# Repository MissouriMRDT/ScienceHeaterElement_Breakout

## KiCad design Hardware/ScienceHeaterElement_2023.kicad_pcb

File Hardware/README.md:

# ScienceHeater_2024
Files for Science Heater

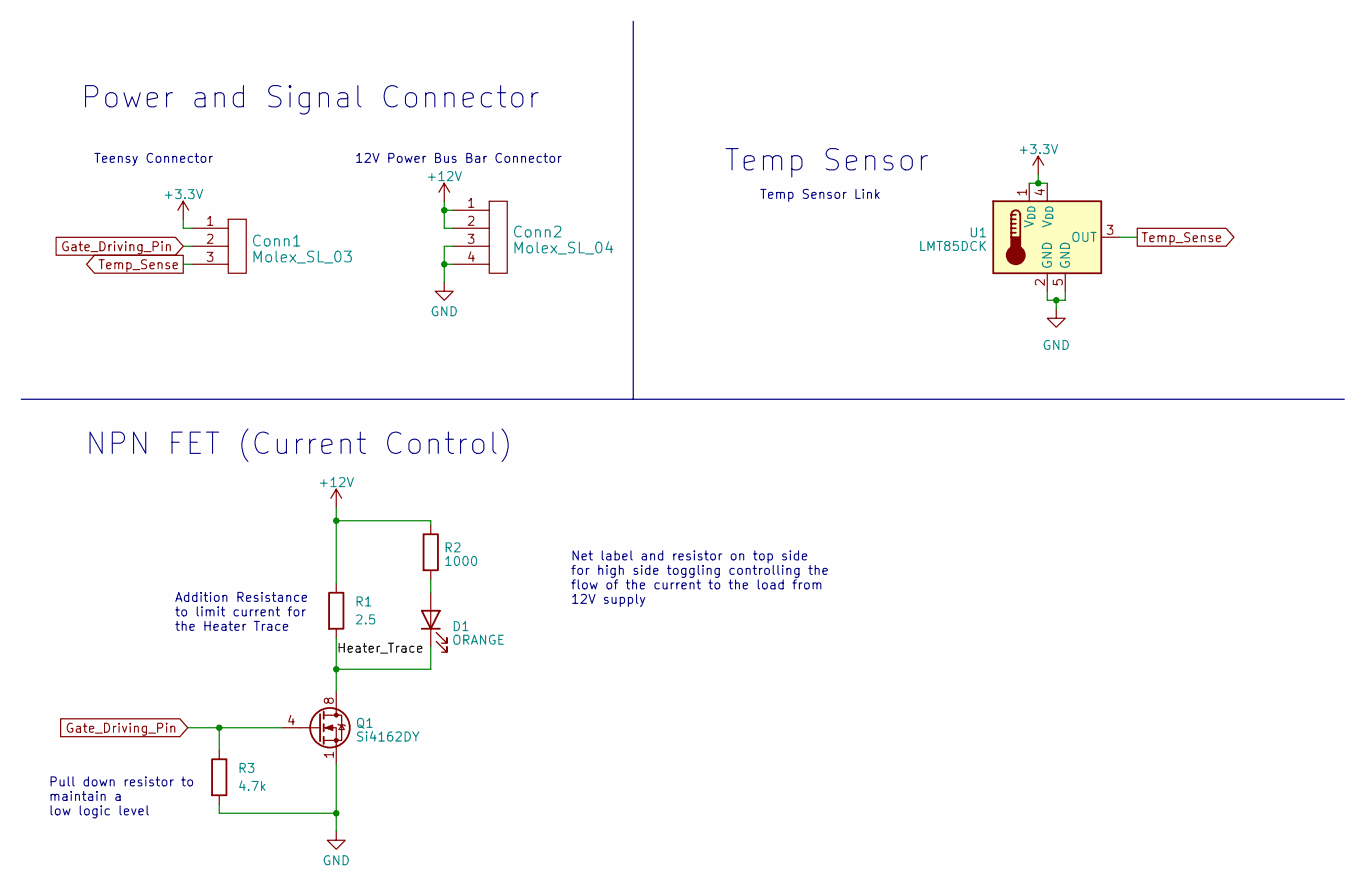
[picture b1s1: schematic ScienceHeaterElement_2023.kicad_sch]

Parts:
Conn1: Molex_SL_03; MOLEX_SL_03_Horizontal
Conn2: Molex_SL_04; MOLEX_SL_04_Horizontal
D1: ORANGE; LED_0603_1608Metric_Pad1.05x0.95mm_HandSolder
Q1: Si4162DY; SOIC-8_3.9x4.9mm_P1.27mm
R1: 2.5; TO-220-2_Horizontal_TabDown
R2: 1000; R_0603_1608Metric_Pad0.98x0.95mm_HandSolder
R3: 4.7k; R_0603_1608Metric_Pad0.98x0.95mm_HandSolder
U1: LMT85DCK; SOT-353_SC-70-5

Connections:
+3.3V: Conn1.1, U1.1 (V_{DD}), U1.4 (V_{DD})
+12V: Conn2.1, Conn2.2, R1.1, R2.1
/Heater_Trace: D1.1 (K), Q1.5 (D), Q1.6 (D), Q1.7 (D), Q1.8 (D), R1.2
GND: Conn2.3, Conn2.4, Q1.1 (S), Q1.2 (S), Q1.3 (S), R3.2, U1.2 (GND), U1.5 (GND)
Gate_Driving_Pin: Conn1.2, Q1.4 (G), R3.1
unnamed: D1.2 (A), R2.2
Temp_Sense: Conn1.3, U1.3 (OUT)

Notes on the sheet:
Addition Resistance to limit current for the Heater Trace
12V Power Bus Bar Connector
Net label and resistor on top side for high side toggling controlling the flow of the current to the load from 12V supply
Temp Sensor Link
Teensy Connector
Power and Signal Connector
NPN FET (Current Control)
Temp Sensor
Pull down resistor to maintain a low logic level

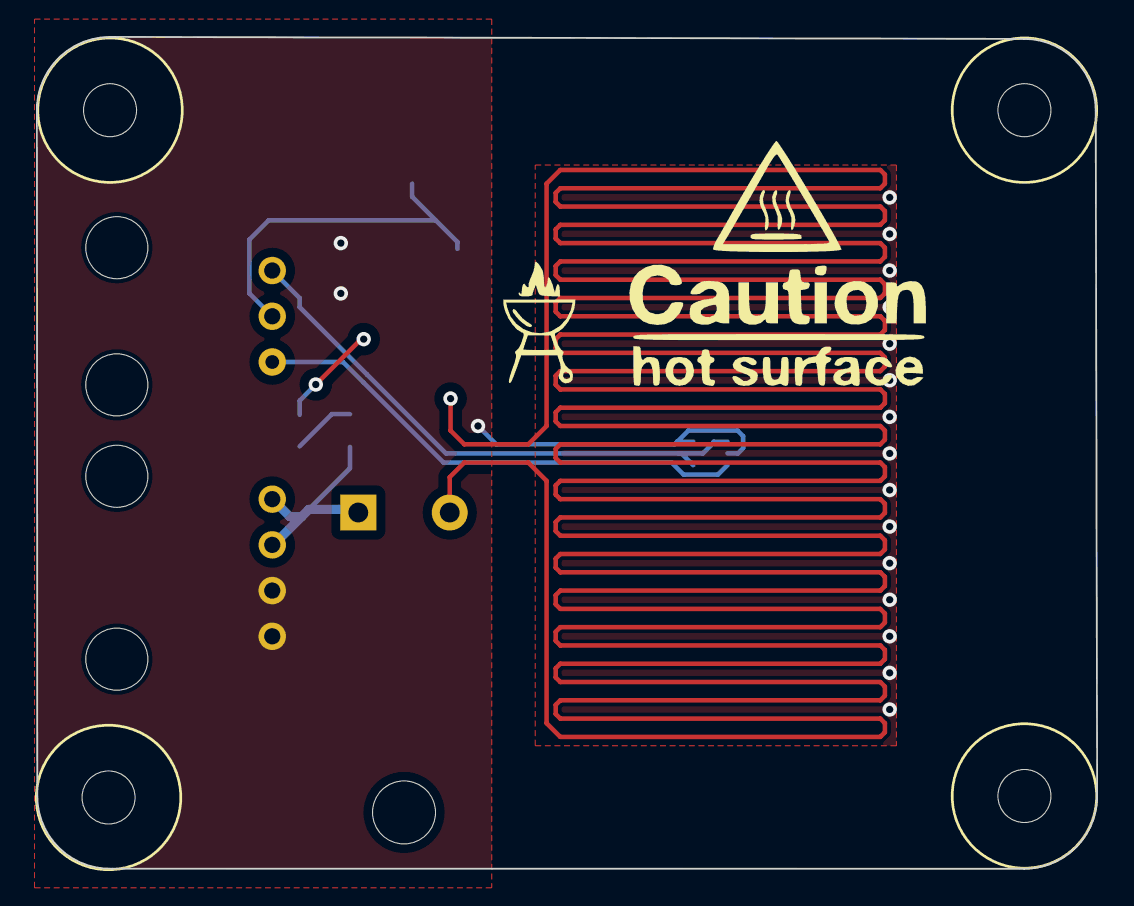
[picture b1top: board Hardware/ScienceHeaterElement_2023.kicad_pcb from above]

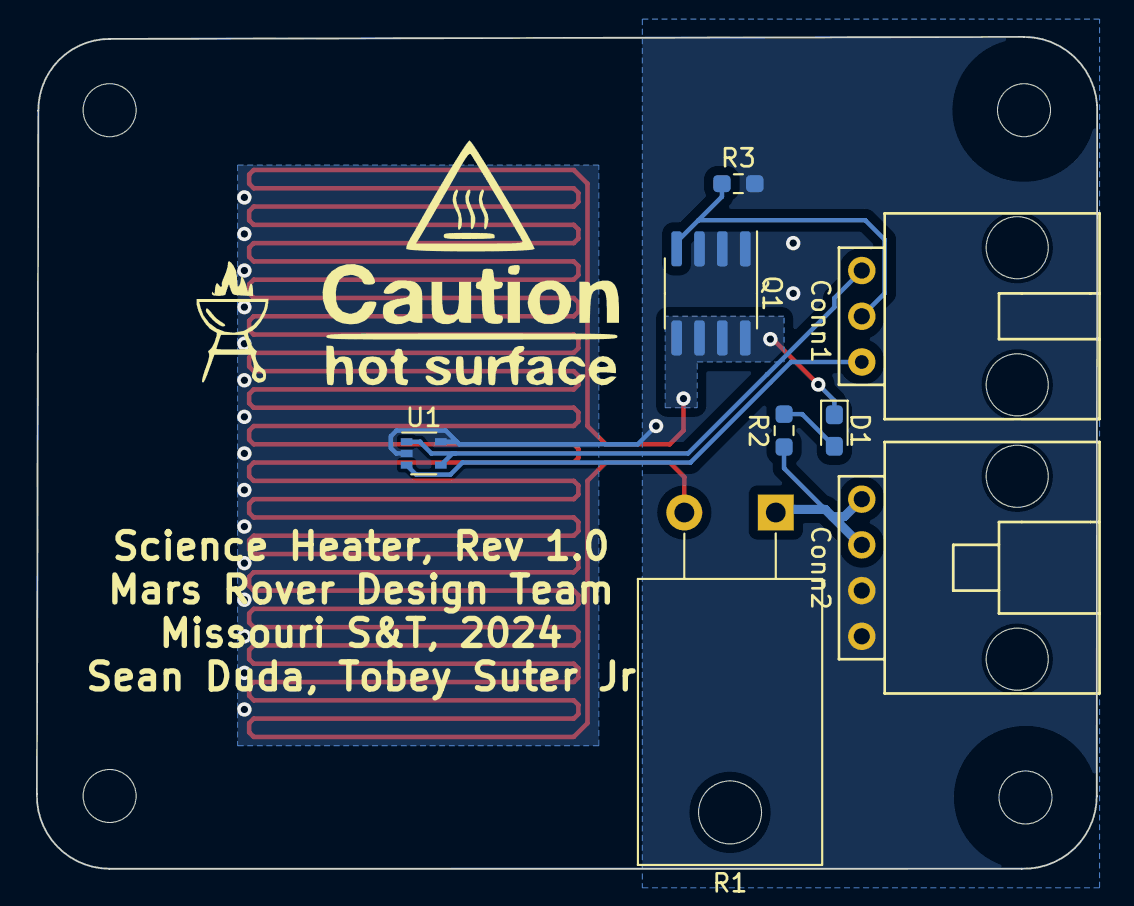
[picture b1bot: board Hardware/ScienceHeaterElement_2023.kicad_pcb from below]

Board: 2 copper layers, 58.9 x 46.2 mm, 8 parts (8 on the bottom side), 7 nets.

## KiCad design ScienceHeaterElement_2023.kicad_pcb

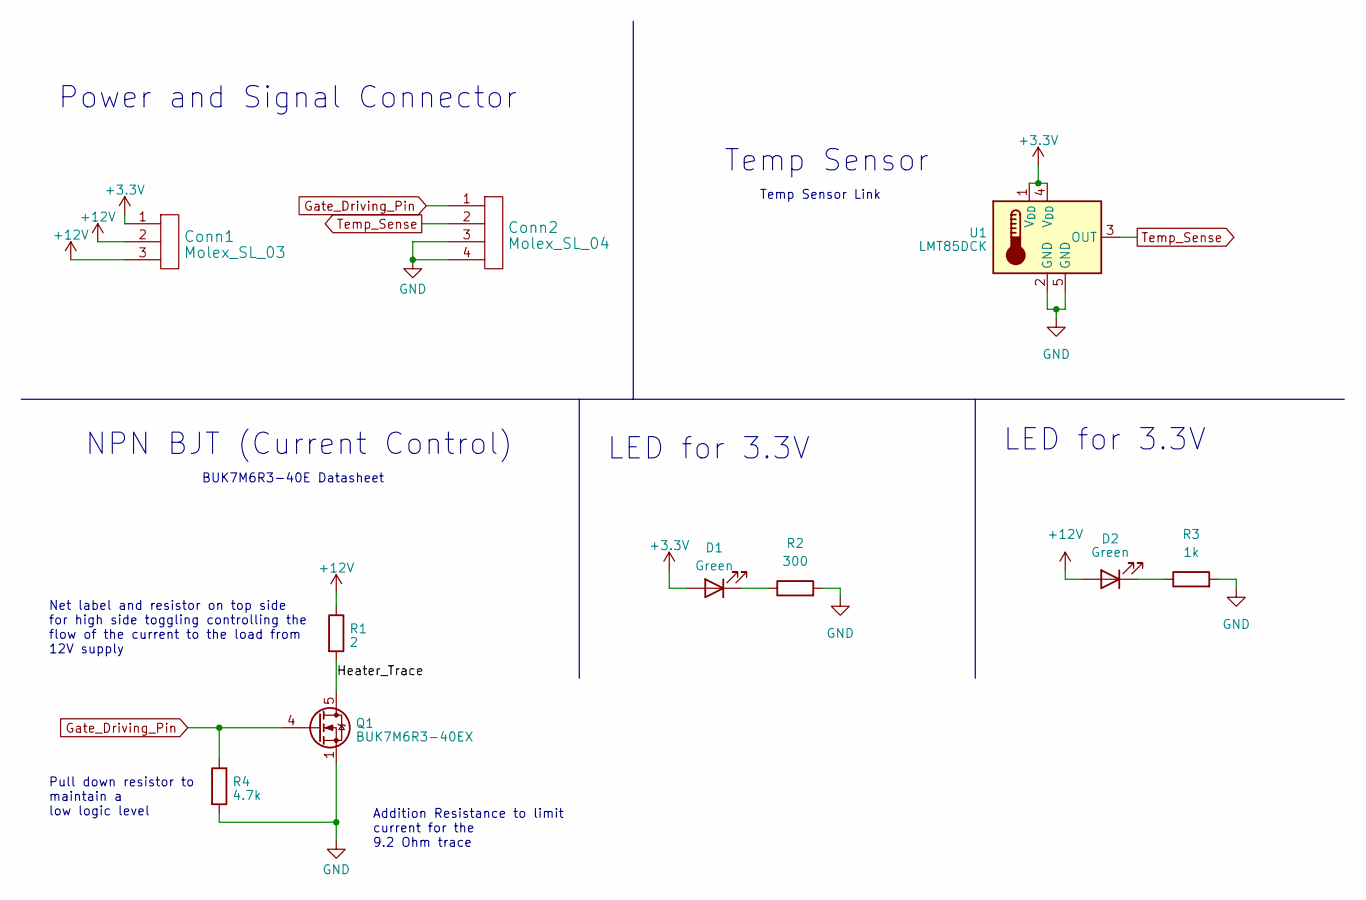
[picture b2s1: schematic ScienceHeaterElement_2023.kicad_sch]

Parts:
Conn1: Molex_SL_03; MOLEX_SL_03_Horizontal
Conn2: Molex_SL_04; MOLEX_SL_04_Horizontal
D1, D2: Green; LED_0603_1608Metric_Pad1.05x0.95mm_HandSolder
Q1: BUK7M6R3-40EX; LFPAK33
R1: 2; R_0603_1608Metric_Pad0.98x0.95mm_HandSolder
R2: 300; R_0603_1608Metric_Pad0.98x0.95mm_HandSolder
R3: 1k; R_0603_1608Metric_Pad0.98x0.95mm_HandSolder
R4: 4.7k; R_0603_1608Metric_Pad0.98x0.95mm_HandSolder
U1: LMT85DCK; SOT-353_SC-70-5

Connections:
+3.3V: Conn1.1, D1.2 (A), U1.1 (V_{DD}), U1.4 (V_{DD})
+12V: Conn1.2, Conn1.3, D2.2 (A), R1.1
/Heater_Trace: Q1.5 (D), R1.2
GND: Conn2.3, Conn2.4, Q1.1 (S), Q1.2 (S), Q1.3 (S), R2.2, R3.2, R4.2, U1.2 (GND), U1.5 (GND)
Gate_Driving_Pin: Conn2.1, Q1.4 (G), R4.1
unnamed: D1.1 (K), R2.1
unnamed: D2.1 (K), R3.1
Temp_Sense: Conn2.2, U1.3 (OUT)

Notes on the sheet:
Addition Resistance to limit current for the 9.2 Ohm trace
LED for 3.3V
Net label and resistor on top side for high side toggling controlling the flow of the current to the load from 12V supply
Temp Sensor Link
Power and Signal Connector
BUK7M6R3-40E Datasheet
NPN BJT (Current Control)
Temp Sensor
Pull down resistor to maintain a low logic level

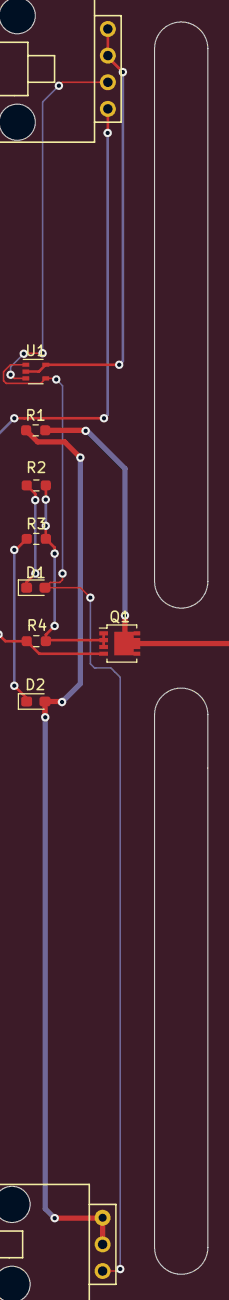
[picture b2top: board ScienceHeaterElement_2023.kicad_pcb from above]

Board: 2 copper layers, 5.1 x 119.4 mm, 10 parts (0 on the bottom side), 8 nets.

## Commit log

2023-09-14 Add files via upload
    Here is the initial design for Science Heater
2023-09-14 Science Heater KiCad
    Inserted Anderson components, a temperature sensor and a molex SL.
2023-09-24 Added BJT Circuit
    Created BJT emitter bias circuit
2023-09-24 PDR
    Changed BJT circuit
2023-09-28 Added LEDs and Resistor values
    Added LEDs and Resistor values
2023-09-30 Changed LED power and Molex 7 pin
    Changed LED power from two 12V to a 12V and a 3.3V to indicate power of the two lines, and changed the molex 7 pin connector to a 3 pin and a 4 pin
2023-10-06 Switched BJT to MOSFET
    Switched to a MOSFET from a BJT. The testing for the BJT gave us unusable results for controlling the current flow through the BJT so we switched to a MOSFET which allows easier controls of the heati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
2023-10-11 Changed MOSFET Circuit to High Side toggle
    Changed MOSFET Circuit to High Side toggling circuit to allow for proper control from the teensy
2023-10-15 Created PCB traces
    Created PCB traces for Science Heater with components placed
2023-10-16 Updated KiCad files and adjusted schematic to meet new requirements
    Updated KiCad files and adjusted schematic to meet new requirements such as an LED in series to indicate Heater trace power
2023-10-16 Updated save from last push
    Updated save issue from last push. This has all the necessary schematic changes
2023-10-19 Schematic Rework
    Moved all devices to the back side of the board. Compressed the board down to a smaller area. Added heat traces and created a keep out area.
2023-10-23 Fixed edge cuts and ground plane
    Fixed edge cuts to rounded edges and created one ground plane and then filled the area.
2023-11-02 Updated Silkscreen
    Updated silkscreen with warning symbols
2023-11-02 Edited heater traces and blockout area
    Increased the blockout area to a .75 by .75 and edited the heater traces to fit the new area. Added text to label the board. Moved temp sensor closer to the heater traces.
2023-11-02 Changed overall size and heating trace area
    Changed size and heating trace area to more effectively heat the microfluidic chips
2023-11-05 Completed Changes
    Completed final changes such as trace work, flipped components, changed gnd keep out
2023-11-06 Updated layout for order
2023-11-06 Generated Gerbs
2023-11-06 Add back mounting holes and regenerate Gerbs
2023-11-07 Changed Temp Sensor plane to GND
    Changed Temp sensor plane to GND and added GND vias between front and back layers
2023-11-08 Expanded GND plane past heater trace area
    Extended GND plane past heater trace area and fixed GND island by connecting GND of temp sensor to GND plane properly
2023-11-09 Replaced current limiting resistor
    Replaced current limiting resistor with 2.5 Ohm resistor and changed the resistor package
2023-11-09 Moved silkscreen labels
    Moved silkscreen labels to where they can be seen properly
2023-11-14 Generated Gerber Files
    Generated Gerber Files to send to JLCPCB
